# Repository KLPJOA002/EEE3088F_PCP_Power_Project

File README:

# Micromouse Power Subsystem – EEE3088F 2025

This repository contains the design files, documentation, and supporting material for the **Micromouse Power Subsystem** designed as part of the EEE3088F course at the University of Cape Town. The subsystem was built to meet a strict set of functional and mechanical requirements under tight budget constraints.

## 🧭 Project Overview

Micromouse is a global robotics competition in which small autonomous robots solve mazes. The UCT EEE3088F course replicates this challenge by requiring students to develop individual subsystems that together build a complete micromouse. This repository documents the design and implementation of the **Power Subsystem**, which is responsible for:

- Bidirectional control of 4 motors (2x 200mA, 2x 500mA)
- Battery charging (with selectable fast and slow charging modes)
- USB-C PD negotiation (9V)
- 5V and 3.3V regulation
- External load switching (2x 1A high-side loads)
- Ultra-low power OFF mode (<30µA)
- INA219 current and voltage monitoring

---

## 🗂 Repository Structure

---

## 🛠 Hardware Requirements

- **Battery**: 3.7V 800mAh LiPo (Micro Robotics)
- **USB PD IC**: HUSB237 for 9V negotiation
- **Motor Driver**: DRV8833 for up to 2A peak per motor
- **Load Switch**: AP22814 (3A capable, overcurrent protected)
- **Battery Monitor**: INA219 over I2C
- **Charging IC**: TP4056-42-ESOP8
- **Voltage Regulators**:
  - 5V: MT3608 Boost Converter
  - 3.3V: AMS1117-3.3 Linear Regulator

---

## ✅ Final Design Summary

- **Footprint**: 82mm × 60mm, mounted via motherboard drill holes
- **Connector**: 2×16 2.54mm header, JST-PH battery connector
- **5V and 3.3V Outputs**:
  - 5V output: up to 1.5A (±5%)
  - 3.3V output: up to 300mA (±5%)
- **Charging Modes**:
  - Slow: ~200mA (logic low on control pin)
  - Fast: ~600mA (logic high on control pin)
- **Sleep Mode**: OFF current draw <30µA, confirmed via test pads
- **INA219**: Allows shunt-based battery current measurement

---

## 🔧 How to Use

1. Open the KiCad project in `/KiCad_Files`.
2. Review schematic, footprints, and PCB constraints.
3. Upload files from `/Gerbers`, `/PnP`, and `/BOM` to JLCPCB.
4. Use `/Screenshots` for evidence of successful upload and configuration.

---

## 📦 JLCPCB Submission

All files have been validated and successfully uploaded to JLCPCB. Screenshots showing the:
- Correct **BOM upload**
- Matching **cart configuration**
are provided in `/Screenshots`.

---

## 👨‍💻 Authors

- **Alex Hillman** `HLLALE010`
- **Joab Kloppers** `KLPJOA002`
Both team members contributed distinct sections of the PCB design and documentation, as per the individual assessment requirements of the course.

- GitHub: [EEE3088F_PCP_Power_Project](https://github.com/KLPJOA002/EEE3088F_PCP_Power_Project)

> Contributions are limited to the Power Subsystem. Design files and reports are subject to UCT's academic integrity policies.

---

## 📜 License

This project is licensed for academic purposes only.

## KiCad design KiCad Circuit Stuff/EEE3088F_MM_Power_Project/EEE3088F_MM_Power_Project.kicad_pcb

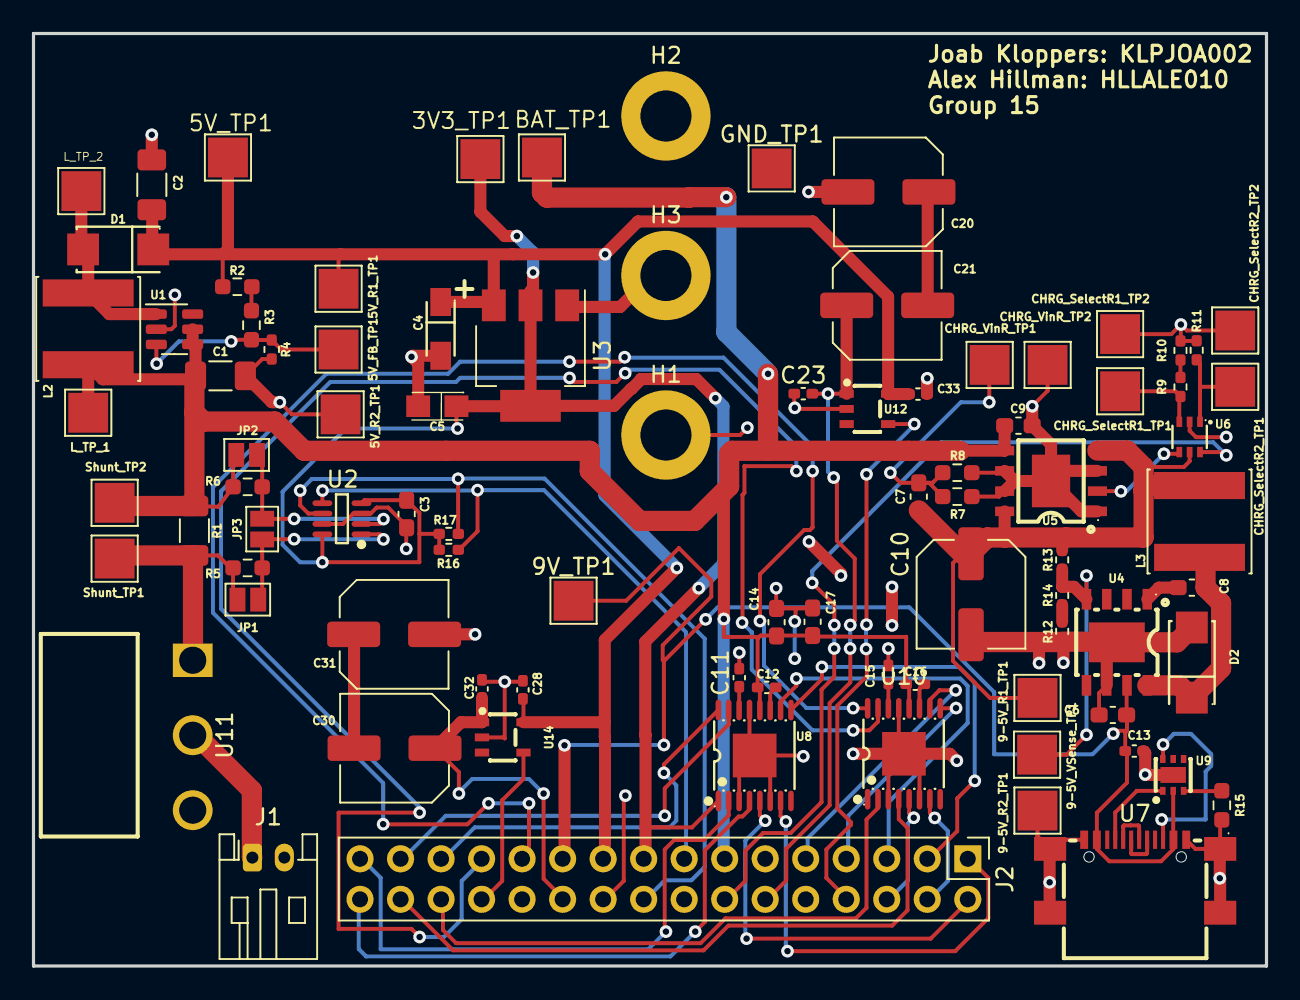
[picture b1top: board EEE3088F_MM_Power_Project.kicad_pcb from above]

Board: 2 copper layers, 77.3 x 58.5 mm, 88 parts (0 on the bottom side), 56 nets.

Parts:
3V3_TP1: 3V3 TP; TestPoint_Pad_2.5x2.5mm
5V_FB_TP1: 5V FB TP; TestPoint_Pad_2.5x2.5mm
5V_R1_TP1: TestPoint_Pad_2.5x2.5mm
5V_R2_TP1: 5V R2 TP; TestPoint_Pad_2.5x2.5mm
5V_TP1: 5V TP; TestPoint_Pad_2.5x2.5mm
9-5V_R1_TP1: 9-5V R1 TP; TestPoint_Pad_2.5x2.5mm
9-5V_R2_TP1: 9-5V R2 TP; TestPoint_Pad_2.5x2.5mm
9-5V_VSense_TP1: 9-5V VSense TP; TestPoint_Pad_2.5x2.5mm
9V_TP1: 9V TP; TestPoint_Pad_2.5x2.5mm
BAT_TP1: BAT TP; TestPoint_Pad_2.5x2.5mm
C1, C2: 22u; C_1206_3216Metric_Pad1.33x1.80mm_HandSolder
C3: 100p; C_0603_1608Metric_Pad1.08x0.95mm_HandSolder
C4: TAJA106K016RNJ; CAP-SMD_L3.2-W1.6-RD-C7171
C5: CA45-A-10V-22UF-K; CASE-A_3216
C6: 4.7u; C_0603_1608Metric_Pad1.08x0.95mm_HandSolder
C7, C9: 10u; C_0603_1608Metric_Pad1.08x0.95mm_HandSolder
C8: 10p; C_0603_1608Metric_Pad1.08x0.95mm_HandSolder
C10: 220u; C_Elec_6.3x7.7
C11, C15: 2.2uF; C_0402_1005Metric_Pad0.74x0.62mm_HandSolder
C12, C16: 10nF; C_0402_1005Metric_Pad0.74x0.62mm_HandSolder
C13, C28, C33: 1uF; C_0402_1005Metric_Pad0.74x0.62mm_HandSolder
C14, C17: 10uF; C_0603_1608Metric_Pad1.08x0.95mm_HandSolder
C20, C21, C30, C31: 220uF; C_Elec_6.3x7.7
C23, C32: 100nF; C_0402_1005Metric_Pad0.74x0.62mm_HandSolder
CHRG_SelectR1_TP1, CHRG_SelectR1_TP2, CHRG_SelectR2_TP1, CHRG_SelectR2_TP2: TestPoint; TestPoint_Pad_2.5x2.5mm
CHRG_VinR_TP1, CHRG_VinR_TP2: TestPoint; TestPoint_Pad_2.5x2.5mm
D1, D2: SS34_C8678; SMA_L4.3-W2.6-LS5.2-RD
GND_TP1: GND TP; TestPoint_Pad_2.5x2.5mm
H1, H2, H3: MountingHole; MountingHole_3.2mm_M3_DIN965_Pad
J1: Conn_01x02; JST_PH_S2B-PH-K_1x02_P2.00mm_Horizontal
J2: Conn_02x16_Odd_Even; PinHeader_2x16_P2.54mm_Vertical
JP1: Possible Filter Res1; SolderJumper-2_P1.3mm_Open_Pad1.0x1.5mm
JP2: Possible Filter Res2; SolderJumper-2_P1.3mm_Open_Pad1.0x1.5mm
JP3: Possible Filter Cap; SolderJumper-2_P1.3mm_Open_Pad1.0x1.5mm
L2, L3: 22u; L_Sunlord_SWPA6045S
L_TP_1, L_TP_2: TestPoint_Pad_2.5x2.5mm
R1: 100m; R_1206_3216Metric_Pad1.30x1.75mm_HandSolder
R2: 220k; R_0603_1608Metric_Pad0.98x0.95mm_HandSolder
R3: 22k; R_0603_1608Metric_Pad0.98x0.95mm_HandSolder
R4: 33k; R_0402_1005Metric_Pad0.72x0.64mm_HandSolder
R5, R6: 0R; R_0603_1608Metric_Pad0.98x0.95mm_HandSolder
R7: 4.7R; R_0603_1608Metric_Pad0.98x0.95mm_HandSolder
R8: 2.2R; R_0603_1608Metric_Pad0.98x0.95mm_HandSolder
R9, R16, R17: 3.3k; R_0402_1005Metric_Pad0.72x0.64mm_HandSolder
R10, R11, R14: 2.2k; R_0402_1005Metric_Pad0.72x0.64mm_HandSolder
R12: 1k; R_0402_1005Metric_Pad0.72x0.64mm_HandSolder
R13: 10k; R_0402_1005Metric_Pad0.72x0.64mm_HandSolder
R15: 75k; R_0603_1608Metric_Pad0.98x0.95mm_HandSolder
Shunt_TP1, Shunt_TP2: TestPoint; TestPoint_Pad_2.5x2.5mm
U1: MT3608; SOT-23-6
U2: INA219AIDCNR; SOT-23-8_L3.0-W1.7-P0.65-LS2.8-BR
U3: AMS1117-3.3; SOT-223-3_TabPin2
U4: TPS5430DDAR; ESOP-8_L4.9-W3.9-P1.27-LS6.0-TL-EP
U5: TP4056; ESOP-8_L4.9-W3.9-P1.27-LS6.0-BL-EP
U6: TS5A3159DCKR; SC-70-6_L2.0-W1.3-P0.65-LS2.1-BL-1
U7: TYPE-C_16P_QTGM027; USB-C-SMD_TYPE-C-16P-QTGM027
U8, U10: DRV8833PWP; TSSOP-16_L5.0-W4.4-P0.65-LS6.4-BL-EP
U9: HUSB237-AA001-DN06R; TDFN-6_L2.0-W2.0-P0.65-TL-EP
U11: SS-12D06-G050; SW-TH_3P-P4.70_SS-12D06-G050
U12, U14: AP22814AW5-7; SOT-25_L3.0-W1.6-P0.95-LS2.8-BL

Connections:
+3V3: 3V3_TP1.1, C3.1, C5.1, J2.17, R16.2, R17.2, U2.4 (VS), U2.8 (A1), U3.2 (VO), U8.1 (nSleep), U10.1 (nSleep)
+5V: 5V_R1_TP1.1, 5V_TP1.1, C2.1, C4.1, C28.2, C33.2, D1.1 (K), J2.19, R2.1, U3.3 (VI), U12.5 (IN), U14.5 (IN)
+9V: 9V_TP1.1, C6.2, C13.2, J2.21, U4.7 (VIN), U7.A4 (VBUS), U7.A9 (VBUS), U9.2 (VUSB)
/AIN1 (U1): J2.27, U8.16 (AIN1)
/AIN1 (U2): J2.23, U10.16 (AIN1)
/AIN2 (U1): J2.29, U8.15 (AIN2)
/AIN2 (U2): J2.25, U10.15 (AIN2)
/AOUT1 (U1): J2.31, U8.2 (AOUT1)
/AOUT1 (U2): J2.28, U10.2 (AOUT1)
/AOUT2 (U1): J2.32, U8.4 (AOUT2)
/AOUT2 (U2): J2.30, U10.4 (AOUT2)
/BIN1 (U1): J2.3, U8.9 (BIN1)
/BIN1 (U2): J2.7, U10.9 (BIN1)
/BIN2 (U1): J2.5, U8.10 (BIN2)
/BIN2 (U2): J2.9, U10.10 (BIN2)
/BOUT1 (U1): J2.1, U8.7 (BOUT1)
/BOUT1 (U2): J2.4, U10.7 (BOUT1)
/BOUT2 (U1): J2.2, U8.5 (BOUT2)
/BOUT2 (U2): J2.6, U10.5 (BOUT2)
/Battery_In_After_Switch: JP1.1 (A), R1.2, R5.1, Shunt_TP1.1, U11.1
/Battery_In_Before_Switch: J1.1, U11.2
/Battery_Out: BAT_TP1.1, C1.1, C9.2, C12.2, C14.1, C16.2, C17.1, J2.13, JP2.2 (B), L2.1, L_TP_1.1, R1.1, R6.1, Shunt_TP2.1, U1.4 (EN), U1.5 (IN), U5.5 (BAT), U8.12 (VM), U10.12 (VM)
/Battey_Charger_VDD: 9-5V_R1_TP1.1, C7.2, C10.1, L3.2, R13.1, U5.4 (VCC), U5.8 (CE), U6.5 (V+)
/CC1: U7.A5 (CC1), U9.1 (CC1)
/CC2: U7.B5 (CC2), U9.6 (CC2)
/CTRL_EXT_LOAD1: J2.26, U14.4 (EN)
/CTRL_EXT_LOAD2: J2.8, U12.4 (EN)
/DN1: U7.A7 (DN1), U7.B7 (DN2)
/DP1: U7.A6 (DP1), U7.B6 (DP2)
/EXT_LOAD1_OUT: C30.1, C32.2, J2.22, U14.1 (OUT)
/EXT_LOAD2_OUT: C20.1, C23.2, J2.12, U12.1 (OUT)
/Fast_Charge_CTRL: J2.14, U6.6 (IN)
/I2C1_SCL: J2.15, R16.1, U2.5 (SCL)
/I2C1_SDA: J2.18, R17.1, U2.6 (SDA)
/PH_Pin: C8.2, D2.1 (K), L3.1, U4.8 (PH)
GND: 5V_R2_TP1.1, 9-5V_R2_TP1.1, C1.2, C2.2, C3.2, C4.2, C5.2, C6.1, C9.1, C10.2, C11.2, C13.1, C14.2, C15.2, C17.2, C21.2, C23.1, C28.1, C31.2, C32.1, C33.1, CHRG_SelectR1_TP2.1, CHRG_SelectR2_TP2.1, CHRG_VinR_TP2.1, D2.2 (A), GND_TP1.1, H1.1, H2.1, H3.1, J1.2, J2.20, J2.24, R4.2, R7.2, R8.2, R10.2, R11.2, R12.1, R15.2, U1.2 (GND), U2.3 (GND), U2.7 (A0), U3.1 (GND), U4.6 (GND), U4.9 (PowerPAD), U5.1 (TEMP), U5.3 (GND), U5.6 (STDBY#), U5.7 (CHRG#), U5.9 (EP), U6.2 (GND), U7.17 (EH), U7.18 (EH), U7.19 (EH), U7.20 (EH), U7.A1 (GND), U7.A12 (GND), U8.3 (AISEN), U8.6 (BISEN), U8.13 (GND), U8.17 (GND), U9.7 (GND), U10.3 (AISEN), U10.6 (BISEN), U10.13 (GND), U10.17 (GND), U11.3, U12.2 (GND), U14.2 (GND)
unnamed: C7.1, CHRG_VinR_TP1.1, R7.1, R8.1
unnamed: C20.2, C21.1
unnamed: C30.2, C31.1
unnamed: D1.2 (A), L2.2, L_TP_2.1, U1.1 (SW)
unnamed: JP1.2 (B), JP3.2 (B), R5.2, U2.1 (IN+)
unnamed: JP2.1 (A), JP3.1 (A), R6.2, U2.2 (IN-)
unnamed: R2.2, R3.1
unnamed: R9.2, R10.1
unnamed: R12.2, R14.2
unnamed: 5V_FB_TP1.1, R3.2, R4.1, U1.3 (FB)
unnamed: C8.1, U4.1 (BOOT)
unnamed: 9-5V_VSense_TP1.1, R13.2, R14.1, U4.4 (VSENSE)
unnamed: U5.2 (PROG), U6.4 (COM)
unnamed: CHRG_SelectR1_TP1.1, R9.1, U6.3 (NC)
unnamed: CHRG_SelectR2_TP1.1, R11.1, U6.1 (NO)
unnamed: C12.1, U8.11 (VCP)
unnamed: C11.1, U8.14 (VINT)
unnamed: R15.1, U9.3 (VSET)
unnamed: C16.1, U10.11 (VCP)
unnamed: C15.1, U10.14 (VINT)

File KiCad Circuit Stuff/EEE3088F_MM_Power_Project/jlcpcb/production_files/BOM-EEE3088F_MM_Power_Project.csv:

Comment,Designator,Footprint,LCSC,Quantity
1k,R12,R_0402_1005Metric_Pad0.72x0.64mm_HandSolder,C11702,1
2.2uF,"C11,C15",C_0402_1005Metric_Pad0.74x0.62mm_HandSolder,C12530,2
22u,"C1,C2",C_1206_3216Metric_Pad1.33x1.80mm_HandSolder,C12891,2
CA45-A-10V-22UF-K,C5,CASE-A_3216,C129272,1
100p,C3,C_0603_1608Metric_Pad1.08x0.95mm_HandSolder,C14858,1
10nF,"C12,C16",C_0402_1005Metric_Pad0.74x0.62mm_HandSolder,C15195,2
100nF,"C23,C32",C_0402_1005Metric_Pad0.74x0.62mm_HandSolder,C1525,2
10p,C8,C_0603_1608Metric_Pad1.08x0.95mm_HandSolder,C1634,1
TP4056,U5,ESOP-8_L4.9-W3.9-P1.27-LS6.0-BL-EP,C16581,1
SS-12D06-G050,U11,SW-TH_3P-P4.70_SS-12D06-G050,C17179521,1
220u,"C10,C20,C21,C30,C31",C_Elec_6.3x7.7,C19100600,5
4.7u,C6,C_0603_1608Metric_Pad1.08x0.95mm_HandSolder,C19666,1
10uF,"C14,C17,C7,C9",C_0603_1608Metric_Pad1.08x0.95mm_HandSolder,C19702,4
0R,"R5,R6",R_0603_1608Metric_Pad0.98x0.95mm_HandSolder,C21189,2
HUSB237-AA001-DN06R,U9,TDFN-6_L2.0-W2.0-P0.65-TL-EP,C22373734,1
2.2R,R8,R_0603_1608Metric_Pad0.98x0.95mm_HandSolder,C22939,1
220k,R2,R_0603_1608Metric_Pad0.98x0.95mm_HandSolder,C22961,1
4.7R,R7,R_0603_1608Metric_Pad0.98x0.95mm_HandSolder,C23164,1
75k,R15,R_0603_1608Metric_Pad0.98x0.95mm_HandSolder,C23242,1
10k,R13,R_0402_1005Metric_Pad0.72x0.64mm_HandSolder,C25744,1
33k,R4,R_0402_1005Metric_Pad0.72x0.64mm_HandSolder,C25779,1
2.2k,"R10,R11,R14",R_0402_1005Metric_Pad0.72x0.64mm_HandSolder,C25879,3
3.3k,"R16,R17,R9",R_0402_1005Metric_Pad0.72x0.64mm_HandSolder,C25890,3
AP22814AW5-7,"U12,U14",SOT-25_L3.0-W1.6-P0.95-LS2.8-BL,C2680321,2
TYPE-C_16P_QTGM027,U7,USB-C-SMD_TYPE-C-16P-QTGM027,C2681552,1
22k,R3,R_0603_1608Metric_Pad0.98x0.95mm_HandSolder,C31850,1
TS5A3159DCKR,U6,SC-70-6_L2.0-W1.3-P0.65-LS2.1-BL-1,C46388,1
DRV8833PWP,"U10,U8",TSSOP-16_L5.0-W4.4-P0.65-LS6.4-BL-EP,C50506,2
1uF,"C13,C28,C33",C_0402_1005Metric_Pad0.74x0.62mm_HandSolder,C52923,3
AMS1117-3.3,U3,SOT-223-3_TabPin2,C6186,1
TAJA106K016RNJ,C4,CAP-SMD_L3.2-W1.6-RD-C7171,C7171,1
100m,R1,R_1206_3216Metric_Pad1.30x1.75mm_HandSolder,C7467250,1
22u,"L2,L3",L_Sunlord_SWPA6045S,C83454,2
MT3608,U1,SOT-23-6,C84817,1
SS34_C8678,"D1,D2",SMA_L4.3-W2.6-LS5.2-RD,C8678,2
INA219AIDCNR,U2,SOT-23-8_L3.0-W1.7-P0.65-LS2.8-BR,C87469,1
TPS5430DDAR,U4,ESOP-8_L4.9-W3.9-P1.27-LS6.0-TL-EP,C9864,1

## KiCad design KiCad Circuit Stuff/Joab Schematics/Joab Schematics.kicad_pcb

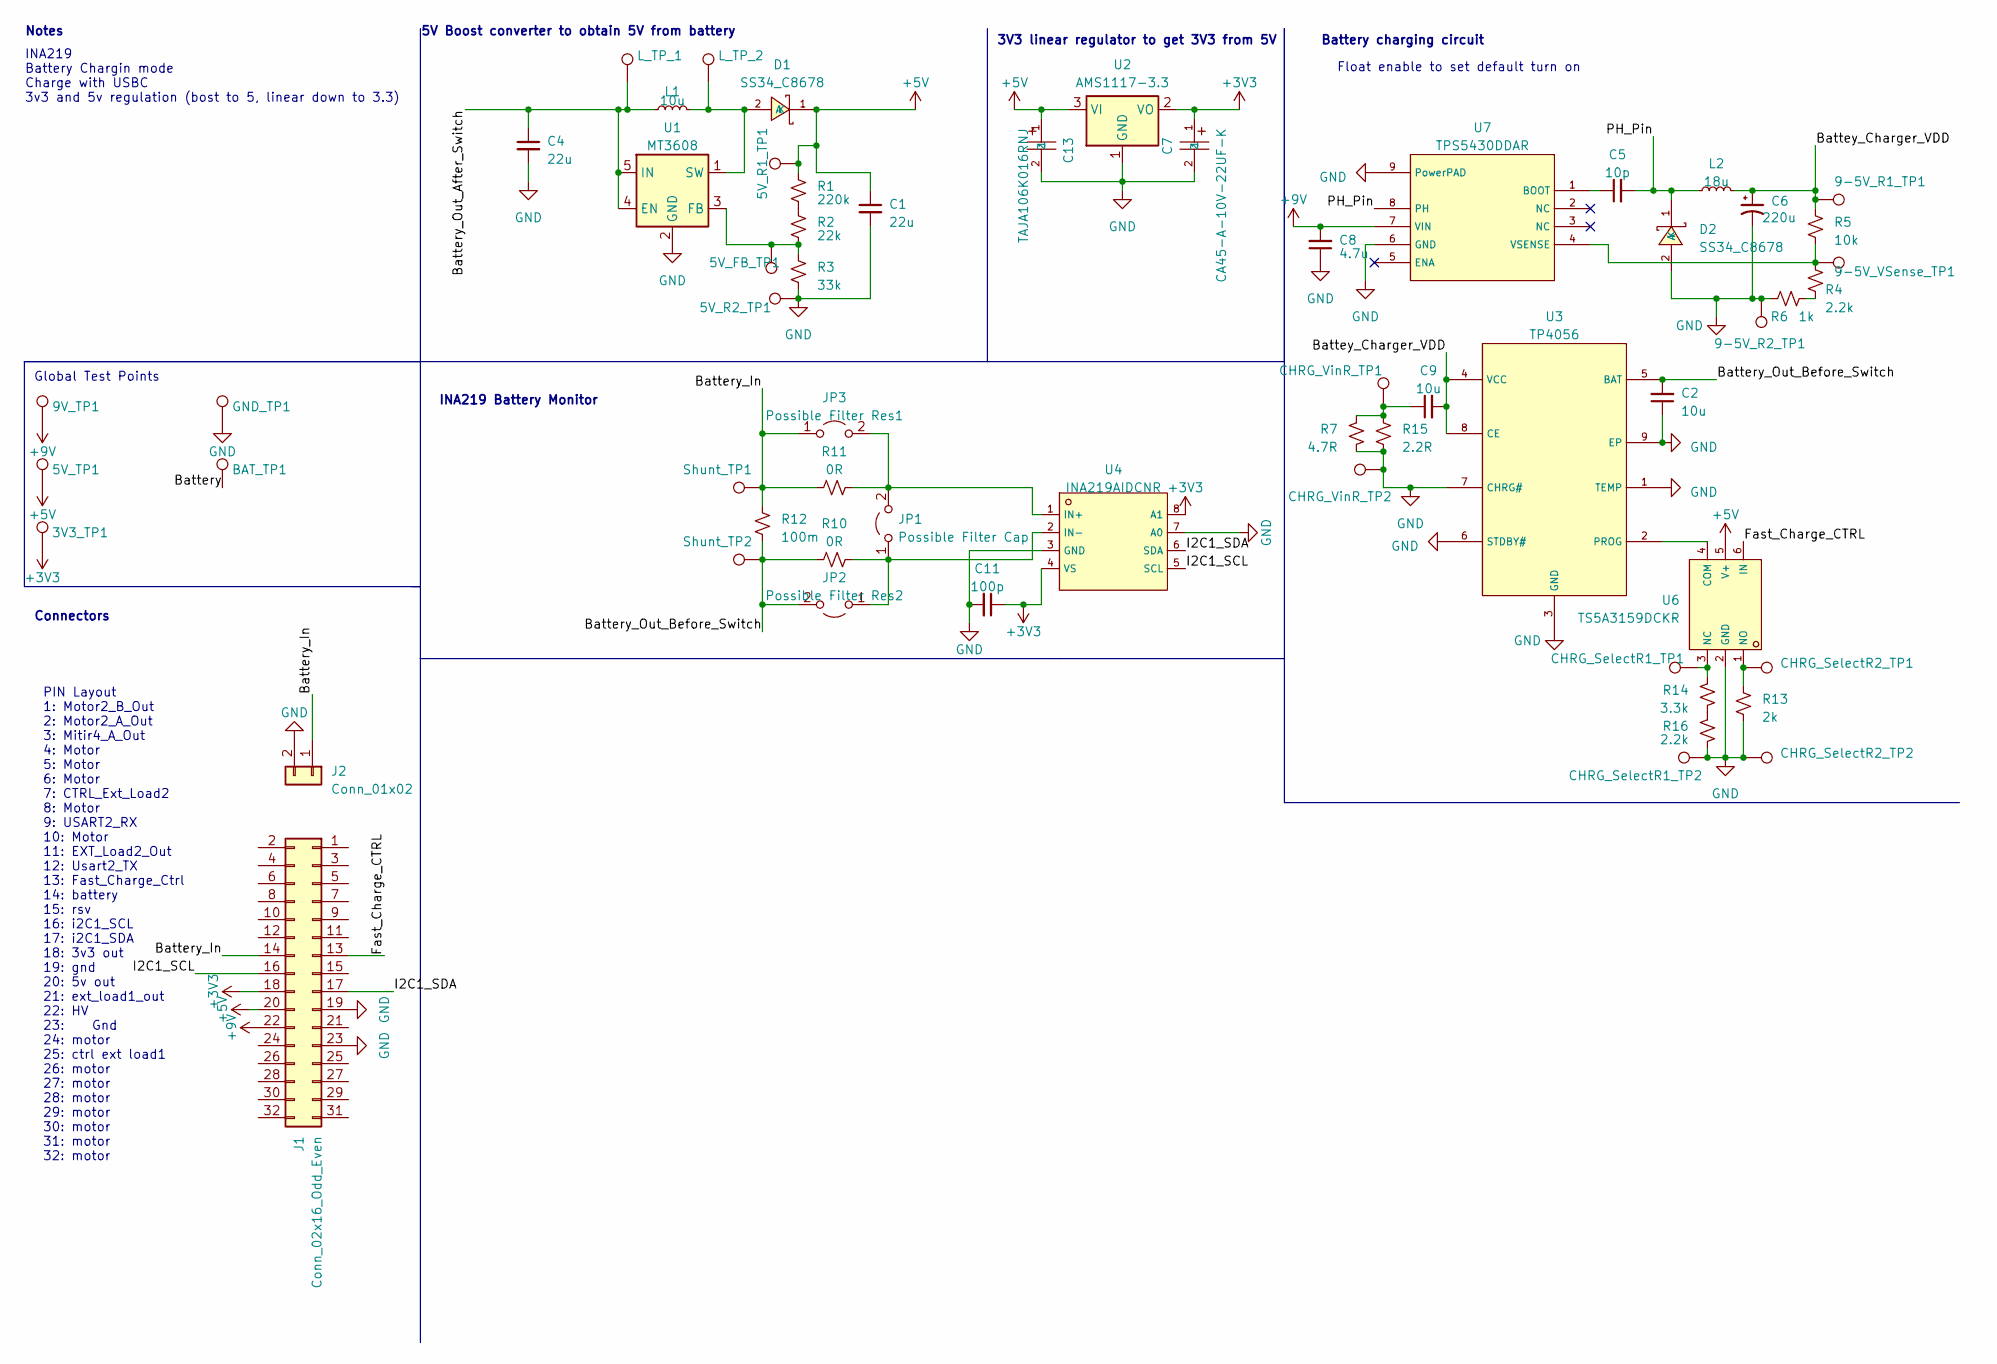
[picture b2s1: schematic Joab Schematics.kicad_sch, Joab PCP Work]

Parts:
3V3_TP1: 3V3 TP; TestPoint_Pad_2.5x2.5mm
5V_FB_TP1: 5V FB TP; TestPoint_Pad_2.5x2.5mm
5V_R1_TP1: TestPoint_Pad_2.5x2.5mm
5V_R2_TP1: 5V R2 TP; TestPoint_Pad_2.5x2.5mm
5V_TP1: 5V TP; TestPoint_Pad_2.5x2.5mm
9-5V_R1_TP1: 9-5V R1 TP; TestPoint_Pad_2.5x2.5mm
9-5V_R2_TP1: 9-5V R2 TP; TestPoint_Pad_2.5x2.5mm
9-5V_VSense_TP1: 9-5V VSense TP; TestPoint_Pad_2.5x2.5mm
9V_TP1: 9V TP; TestPoint_Pad_2.5x2.5mm
BAT_TP1: BAT TP; TestPoint_Pad_2.5x2.5mm
C1, C4: 22u; C_1206_3216Metric_Pad1.33x1.80mm_HandSolder; LCSC C12891
C2, C9: 10u; C_0603_1608Metric_Pad1.08x0.95mm_HandSolder; LCSC C19702
C5: 10p; C_0603_1608Metric_Pad1.08x0.95mm_HandSolder; LCSC C1634
C6: 220u; C_Elec_6.3x7.7; LCSC C19100600
C7: CA45-A-10V-22UF-K; CASE-A_3216; LCSC C129272
C8: 4.7u; C_0603_1608Metric_Pad1.08x0.95mm_HandSolder; LCSC C19666
C11: 100p; C_0603_1608Metric_Pad1.08x0.95mm_HandSolder; LCSC C14858
C13: TAJA106K016RNJ; CAP-SMD_L3.2-W1.6-RD-C7171; LCSC C7171
CHRG_SelectR1_TP1, CHRG_SelectR1_TP2, CHRG_SelectR2_TP1, CHRG_SelectR2_TP2: TestPoint; TestPoint_Pad_2.5x2.5mm
CHRG_VinR_TP1, CHRG_VinR_TP2: TestPoint; TestPoint_Pad_2.5x2.5mm
D1, D2: SS34_C8678; SMA_L4.3-W2.6-LS5.2-RD; LCSC C8678
GND_TP1: GND TP; TestPoint_Pad_2.5x2.5mm
J1: Conn_02x16_Odd_Even; PinHeader_2x16_P2.54mm_Vertical
J2: Conn_01x02; JST_PH_B2B-PH-K_1x02_P2.00mm_Vertical
JP1: Possible Filter Cap; SolderJumper-2_P1.3mm_Open_Pad1.0x1.5mm
JP2: Possible Filter Res2; SolderJumper-2_P1.3mm_Open_Pad1.0x1.5mm
JP3: Possible Filter Res1; SolderJumper-2_P1.3mm_Open_Pad1.0x1.5mm
L1: 10u; L_Changjiang_FNR4030S; LCSC C167879
L2: 18u; L_Changjiang_FNR4030S; LCSC C167882
L_TP_1, L_TP_2: TestPoint_Pad_2.5x2.5mm
R1: 220k; R_0603_1608Metric_Pad0.98x0.95mm_HandSolder; LCSC C22961
R2: 22k; R_0603_1608Metric_Pad0.98x0.95mm_HandSolder; LCSC C31850
R3: 33k; R_0402_1005Metric_Pad0.72x0.64mm_HandSolder; LCSC C25779
R4, R16: 2.2k; R_0402_1005Metric_Pad0.72x0.64mm_HandSolder; LCSC C25879
R5: 10k; R_0402_1005Metric_Pad0.72x0.64mm_HandSolder; LCSC C25744
R6: 1k; R_0402_1005Metric_Pad0.72x0.64mm_HandSolder; LCSC C11702
R7: 4.7R; R_0603_1608Metric_Pad0.98x0.95mm_HandSolder; LCSC C23164
R10, R11: 0R; R_0603_1608Metric_Pad0.98x0.95mm_HandSolder; LCSC C21189
R12: 100m; R_0402_1005Metric_Pad0.72x0.64mm_HandSolder; LCSC C7467250
R13: 2k; R_0402_1005Metric_Pad0.72x0.64mm_HandSolder; LCSC C4109
R14: 3.3k; R_0402_1005Metric_Pad0.72x0.64mm_HandSolder; LCSC C25890
R15: 2.2R; R_0603_1608Metric_Pad0.98x0.95mm_HandSolder; LCSC C22939
Shunt_TP1, Shunt_TP2: TestPoint; TestPoint_Pad_2.5x2.5mm
U1: MT3608; SOT-23-6; LCSC C84817
U2: AMS1117-3.3; SOT-223-3_TabPin2; LCSC C6186
U3: TP4056; ESOP-8_L4.9-W3.9-P1.27-LS6.0-BL-EP; LCSC C16581
U4: INA219AIDCNR; SOT-23-8_L3.0-W1.7-P0.65-LS2.8-BR; LCSC C87469
U6: TS5A3159DCKR; SC-70-6_L2.0-W1.3-P0.65-LS2.1-BL-1; LCSC C46388
U7: TPS5430DDAR; ESOP-8_L4.9-W3.9-P1.27-LS6.0-TL-EP; LCSC C9864

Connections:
+3V3: 3V3_TP1.1, C7.1, C11.1, J1.18, U2.2 (VO), U4.4 (VS), U4.8 (A1)
+5V: 5V_R1_TP1.1, 5V_TP1.1, C1.1, C13.1, D1.1 (K), J1.20, R1.1, U2.3 (VI), U6.5 (V+)
+9V: 9V_TP1.1, C8.2, J1.22, U7.7 (VIN)
/Battery: BAT_TP1.1
/Battery_In: J1.14, J2.1, JP3.1 (A), R11.1, R12.2, Shunt_TP1.1
/Battery_Out_After_Switch: C4.1, L1.1, L_TP_1.1, U1.4 (EN), U1.5 (IN)
/Battery_Out_Before_Switch: C2.2, JP2.2 (B), R10.1, R12.1, Shunt_TP2.1, U3.5 (BAT)
/Battey_Charger_VDD: 9-5V_R1_TP1.1, C6.1, C9.2, L2.2, R5.1, U3.4 (VCC), U3.8 (CE)
/Fast_Charge_CTRL: J1.13, U6.6 (IN)
/I2C1_SCL: J1.16, U4.5 (SCL)
/I2C1_SDA: J1.17, U4.6 (SDA)
/PH_Pin: C5.2, D2.1 (K), L2.1, U7.8 (PH)
GND: 5V_R2_TP1.1, 9-5V_R2_TP1.1, C1.2, C2.1, C4.2, C6.2, C7.2, C8.1, C11.2, C13.2, CHRG_SelectR1_TP2.1, CHRG_SelectR2_TP2.1, CHRG_VinR_TP2.1, D2.2 (A), GND_TP1.1, J1.19, J1.23, J2.2, R3.2, R6.1, R7.2, R13.2, R15.2, R16.2, U1.2 (GND), U2.1 (GND), U3.1 (TEMP), U3.3 (GND), U3.6 (STDBY#), U3.7 (CHRG#), U3.9 (EP), U4.3 (GND), U4.7 (A0), U6.2 (GND), U7.6 (GND), U7.9 (PowerPAD)
unnamed: C9.1, CHRG_VinR_TP1.1, R7.1, R15.1
unnamed: D1.2 (A), L1.2, L_TP_2.1, U1.1 (SW)
unnamed: JP1.1 (A), JP2.1 (A), R10.2, U4.2 (IN-)
unnamed: JP1.2 (B), JP3.2 (B), R11.2, U4.1 (IN+)
unnamed: R1.2, R2.1
unnamed: R4.2, R6.2
unnamed: R14.2, R16.1
unnamed: 5V_FB_TP1.1, R2.2, R3.1, U1.3 (FB)
unnamed: U3.2 (PROG), U6.4 (COM)
unnamed: CHRG_SelectR1_TP1.1, R14.1, U6.3 (NC)
unnamed: CHRG_SelectR2_TP1.1, R13.1, U6.1 (NO)
unnamed: C5.1, U7.1 (BOOT)
unnamed: 9-5V_VSense_TP1.1, R4.1, R5.2, U7.4 (VSENSE)

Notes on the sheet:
INA219 Battery Chargin mode Charge with USBC 3v3 and 5v regulation (bost to 5, linear down to 3.3)
PIN Layout 1: Motor2_B_Out 2: Motor2_A_Out 3: Mitir4_A_Out 4: Motor 5: Motor 6: Motor 7: CTRL_Ext_Load2 8: Motor 9: USART2_RX 10: Motor 11: EXT_Load2_Out 12: Usart2_TX 13: Fast_Charge_Ctrl 14: battery 15: rsv 16: i2C1_SCL 17: i2C1_SDA 18: 3v3 out 19: gnd 20: 5v out 21: ext_load1_out 22: HV 23: Gnd 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
Global Test Points
Float enable to set default turn on
Notes
5V Boost converter to obtain 5V from battery
3V3 linear regulator to get 3V3 from 5V
Battery charging circuit
Connectors
INA219 Battery Monitor

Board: 2 copper layers, 60 parts (0 on the bottom side), 25 nets, no tracks yet.

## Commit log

2025-03-12 Added Kicad Files
2025-03-12 added comment
2025-03-12 Added two new schematics for each person to work independantly
2025-03-12 Added some readmes for each person
2025-03-20 Added some things
2025-03-20 I added a driver IC
2025-03-20 Did some voltage Regulation for 5v without calculating values
2025-03-22 Added 5V and 3v3 Regulation, started on battery charging
2025-03-23 DId battery charger, some labeling and components
2025-03-23 Added INA219 monitor (kinda) and added some fixes
2025-03-24 Chaned Charrging IC, Chaned INA219 IC, Changed some other things
2025-03-24 Added Switching for charger
2025-03-25 added some stuff
2025-03-25 Changed some values of resistors, caps and inductors, Also modified some components Still need to finish adding resistors from jlcpcb
2025-03-26 Chose all passive components, added test points to all
2025-03-26 Joab Started Work on main pcb
2025-03-26 Connected All circuits, Ready for pcb design
2025-03-26 Got rid of old switch
2025-03-26 Added something
2025-03-26 Done Significant circuit work
2025-03-27 Did somke more pcb
2025-03-27 Removed D+ and D- to float on the USPD
2025-03-27 Changed inductors and rewired
2025-03-27 Added most of all connections and holes
2025-03-27 finished wiring
2025-03-27 Made some final tweaks, and created gerber files
2025-03-27 added stuff
2025-03-27 Gerbers added
2025-03-27 Changed JST
2025-03-27 added final bom
2025-03-27 added bom again
2025-03-27 final
2025-03-28 Tweaked some stuff
2025-03-28 redid bom
2025-03-28 Change silkscreen and drill hole issues
2025-03-28 added new bom
2025-04-22 Added some lables in Joab Schematic
2025-04-24 changed some stuff
2025-04-25 Added ReadMe and other minor changes
